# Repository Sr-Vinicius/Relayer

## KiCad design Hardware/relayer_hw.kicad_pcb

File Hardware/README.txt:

# Hardware

Kicad Project, custom user files, and third party user files

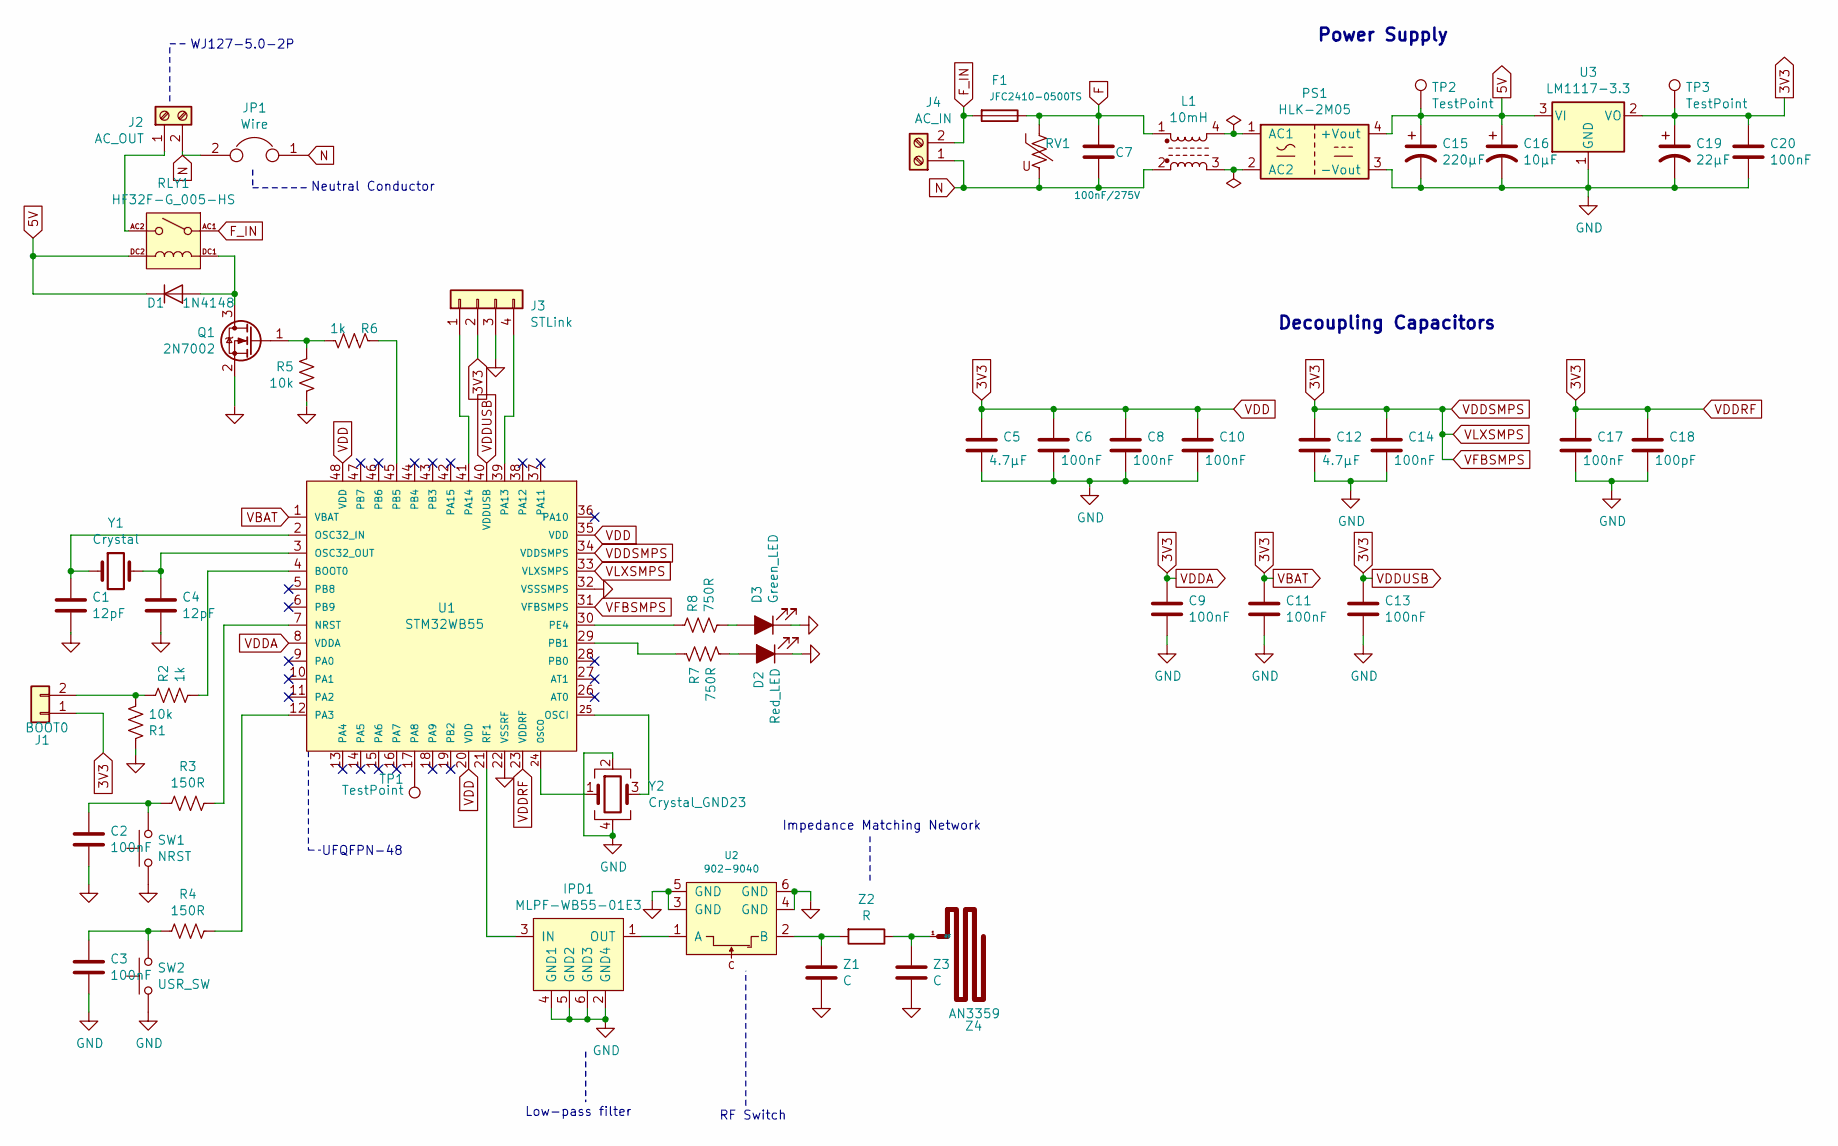
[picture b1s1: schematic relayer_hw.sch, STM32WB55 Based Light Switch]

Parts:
C1, C4: 12pF; C_0402_1005Metric
C2, C3, C6, C8, C9, C10, C11, C13, C14, C17, C20: 100nF; C_0402_1005Metric
C5, C12: 4.7μF; C_0402_1005Metric
C7: 100nF/275V; C_Rect_L18.0mm_W6.0mm_P15.00mm_FKS3_FKP3
C15: 220μF; cap_elec
C16: 10μF; CAPC1608X90
C18: 100pF; C_0402_1005Metric
C19: 22μF; CAPC1608X90
D1: 1N4148; SODFL1608X70N
D2: Red_LED; LED_D5.0mm_Clear
D3: Green_LED; LED_D5.0mm_Clear
F1: JFC2410-0500TS; Fuse_2010_5025Metric_Pad1.52x2.65mm_HandSolder
IPD1: MLPF-WB55-01E3
J1: BOOT0; PinHeader_1x02_P2.54mm_Vertical
J2: AC_OUT; TerminalBlock_bornier-2_P5.08mm
J3: STLink; PinHeader_1x04_P2.54mm_Vertical
J4: AC_IN; TerminalBlock_bornier-2_P5.08mm
JP1: Wire; neutral_wire
L1: 10mH; FL2D-Z5-103
PS1: HLK-2M05
Q1: 2N7002; SOT-23
R1, R5: 10k; R_0805_2012Metric_Pad1.15x1.40mm_HandSolder
R2, R6: 1k; R_0805_2012Metric_Pad1.15x1.40mm_HandSolder
R3, R4: 150R; R_0805_2012Metric_Pad1.15x1.40mm_HandSolder
R7, R8: 750R; R_0805_2012Metric_Pad1.15x1.40mm_HandSolder
RLY1: HF32F-G_005-HS; HF32F-G005-HS
RV1: Varistor_US; RV_Disc_D12mm_W6.1mm_P7.5mm
SW1: NRST; 1TS002B-1900-4300-CT
SW2: USR_SW; SW_PUSH_6mm_H13mm
TP1: TestPoint; PinHeader_1x01_P2.54mm_Vertical
TP2, TP3: TestPoint; TestPoint_Pad_D1.0mm
U1: STM32WB55; QFN50P700X700X60-49N
U2: 902-9040
U3: LM1117-3.3; SOT-223
Y1: Crystal; Crystal_SMD_2012-2Pin_2.0x1.2mm_HandSoldering
Y2: Crystal_GND23; Crystal_SMD_3225-4Pin_3.2x2.5mm_HandSoldering
Z1, Z3: C; R_0402_1005Metric
Z2: R; R_0402_1005Metric
Z4: AN3359; AN3359_antenna

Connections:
3V3: C5.1, C6.1, C8.1, C9.1, C10.1, C11.1, C12.1, C13.1, C14.1, C17.1, C18.1, C19.1, C20.1, J1.1, J3.2, TP3.1, U1.1 (VBAT), U1.8 (VDDA~), U1.20 (VDD), U1.23 (VDDRF~), U1.31 (VFBSMPS), U1.33 (VLXSMPS), U1.34 (VDDSMPS), U1.35 (VDD), U1.40 (VDDUSB), U1.48 (VDD), U3.2 (VO), U3.4; also elsewhere on the board
5V: C15.1, C16.1, D1.1 (K), PS1.4 (+Vout), RLY1.DC2, TP2.1, U3.3 (VI)
F: C7.1, F1.1, L1.1, RV1.1
F_IN: F1.2, J4.2, RLY1.AC1
GND: C1.2, C2.1, C3.1, C4.2, C5.2, C6.2, C8.2, C9.2, C10.2, C11.2, C12.2, C13.2, C14.2, C15.2, C16.2, C17.2, C18.2, C19.2, C20.2, D2.1 (K), D3.1 (K), IPD1.2 (GND4), IPD1.4 (GND1), IPD1.5 (GND2), IPD1.6 (GND3), J3.3, PS1.3 (-Vout), Q1.2 (S), R1.2, R5.2, SW1.2, SW2.2, U1.22 (VSSRF), U1.32 (VSSSMPS), U1.49, U2.3 (GND), U2.4 (GND), U2.5 (GND), U2.6 (GND), U3.1 (GND), Y2.2, Y2.4, Z1.2, Z3.2; also elsewhere on the board
N: C7.2, J2.2, J4.1, JP1.1, JP1.2, L1.2, RV1.2
unnamed: C1.1, U1.2 (OSC32_IN), Y1.1
unnamed: C2.2, R3.2, SW1.1
unnamed: C3.2, R4.2, SW2.1
unnamed: C4.1, U1.3 (OSC32_OUT), Y1.2
unnamed: D1.2 (A), Q1.3 (D), RLY1.DC1
unnamed: D2.2 (A), R7.2
unnamed: D3.2 (A), R8.2
unnamed: IPD1.1 (OUT), U2.1 (A)
unnamed: IPD1.3 (IN), U1.21 (RF1)
unnamed 15: J1.2, R1.1, R2.2; also elsewhere on the board
unnamed: J2.1, RLY1.AC2
unnamed 17: J3.1, U1.41 (PA14); also elsewhere on the board
unnamed 18: J3.4, U1.39 (PA13); also elsewhere on the board
unnamed: L1.3, PS1.2 (AC2)
unnamed: L1.4, PS1.1 (AC1)
unnamed: Q1.1 (G), R5.1, R6.2
unnamed: R2.1, U1.4 (BOOT0)
unnamed: R3.1, U1.7 (NRST)
unnamed: R4.1, U1.12 (PA3)
unnamed: R6.1, U1.45 (PB5)
unnamed: R7.1, U1.29 (PB1)
unnamed: R8.1, U1.30 (PE4)
unnamed: TP1.1, U1.17 (PA8)
unnamed: U1.24 (OSCO), Y2.1
unnamed: U1.25 (OSCI), Y2.3
unnamed: U2.2 (B), Z1.1, Z2.2
unnamed: Z2.1, Z3.1, Z4.1

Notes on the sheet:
WJ127-5.0-2P
Low-pass filter
RF Switch
Impedance Matching Network
Power Supply
Decoupling Capacitors
Neutral Conductor
UFQFPN-48

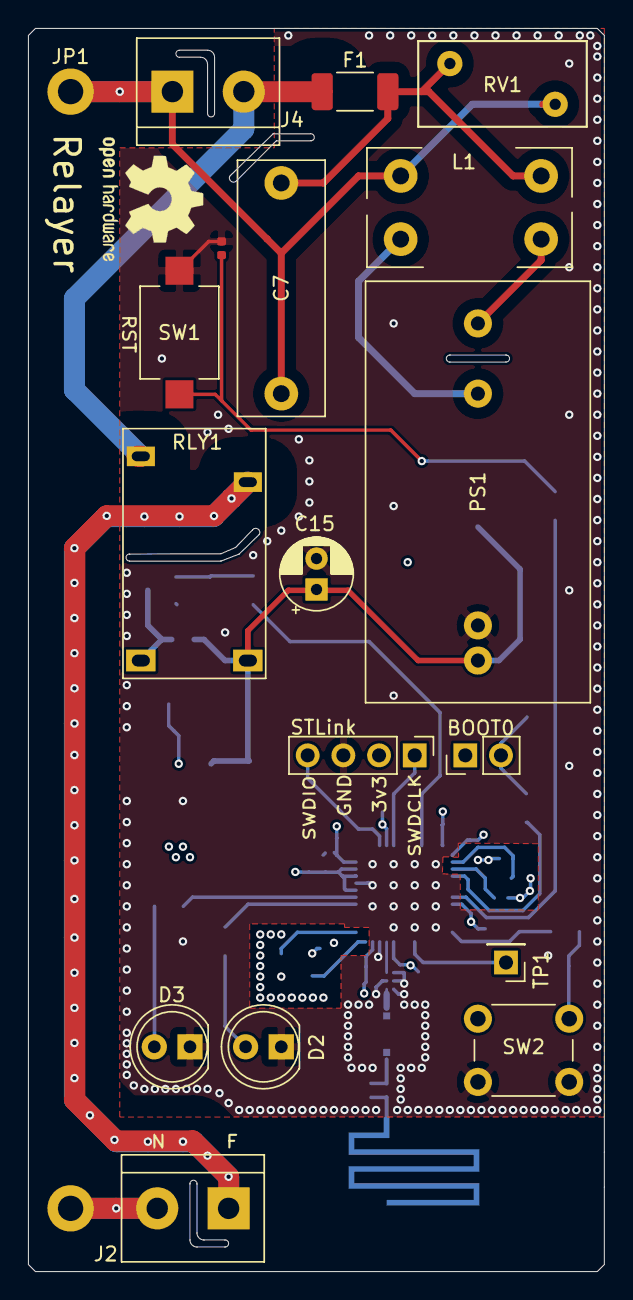
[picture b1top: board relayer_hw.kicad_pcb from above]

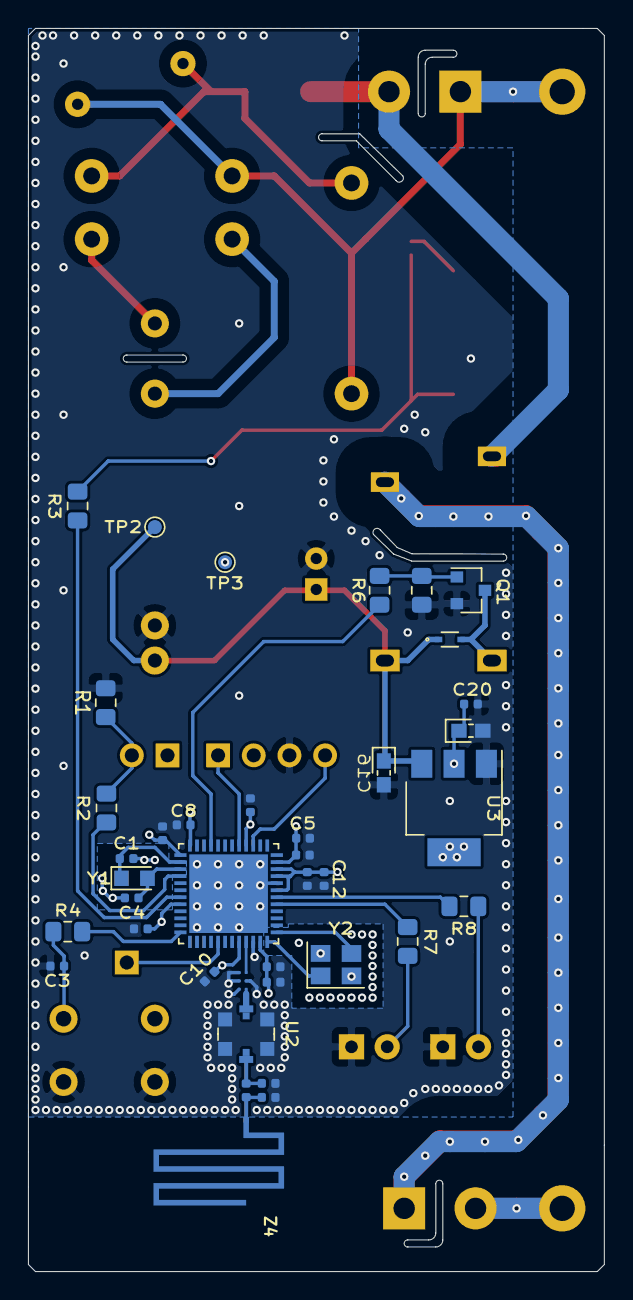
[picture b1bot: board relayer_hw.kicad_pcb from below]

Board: 4 copper layers, 41.0 x 88.5 mm, 57 parts (39 on the bottom side), 33 nets.

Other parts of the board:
BOOT0: BOOT0; PinHeader_1x02_P2.54mm_Vertical
STLink: STLink; PinHeader_1x04_P2.54mm_Vertical

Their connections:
3V3: BOOT0.1, STLink.2; also elsewhere on the board
GND: STLink.3; also elsewhere on the board
unnamed 15: BOOT0.2; also elsewhere on the board
unnamed 17: STLink.1; also elsewhere on the board
unnamed 18: STLink.4; also elsewhere on the board

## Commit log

2021-03-30 Adicionando os repositorios iniciais
2021-04-02 Esquematico do regulador linear da fonte
2021-04-04 Esquematico da fonte (não definitivo)
2021-04-11 Simbolo do STM32WB55 e alimentação do chip (inicio)
2021-04-27 Fonte definitiva/ LEDs sem mosfet driver/ Esquematico reorganizado/ Datasheets
2021-05-06 Circuito RF/ Reorganização prática do hardware
2021-05-09 Associação de datasheets e footprints
2021-05-19 Annotate / ERC
2021-05-21 Correções de limites eletricos e remocao da pasta 'Datasheets'
2021-05-30 Netlist gerada/ Correncao de nets/ Inicio do layout
2021-06-06 Correção nos cristais/Posicionamento dos componentes em andamento
2021-06-08 Rotas dos caps de desacoplamento/ zonas de cobre externas/ posicionamento de componentes
2021-06-12 Ajustes nos caps de desacoplamento/ Primeiras rotas
2021-06-17 Tamanho ajustado para caixa IP67 e rotas completas
2021-06-18 RF via fences
2021-06-23 Conectando nos n conectados / planos de terra e vcc
2021-06-23 Correçoes de pepinos do DRC
2021-06-24 Versao final dos planos de gnd e vcc (?)
2021-06-25 Via stitching
2021-07-06 Correcao nos capacitores/Revisões de nets
2021-07-10 Revisao para especificacoes da JLCPCB
2021-07-14 Deixando a PCB soldavel
2021-07-22 Segunda Revisão
2021-07-24 Aprimoramentos finais
2021-07-24 Terceira revisão
2021-07-28 Revisao 3.1
2022-02-11 Revisao de hardware
